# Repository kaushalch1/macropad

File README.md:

Smart OLED MacroPad

A customizable MacroPad with an OLED display, designed to provide quick access to essential travel and utility tools.

## Features
Google Maps launcher,
Weather information,
Currency converter,
Travel checklist,
OLED display interface,
One-key access to commonly used functions,
Plug-and-play operation,
The customize of buttons is released soon with the help of qmk software.
The oled display shows the time.

## software
kicad
fusion360
qmk

## Parts(or)bom
SEED XIAO board,
4 mx switches,
1 oled 0.91" screen

## Schematics

## PCB

## 3D view

## cad photo

## travel photo

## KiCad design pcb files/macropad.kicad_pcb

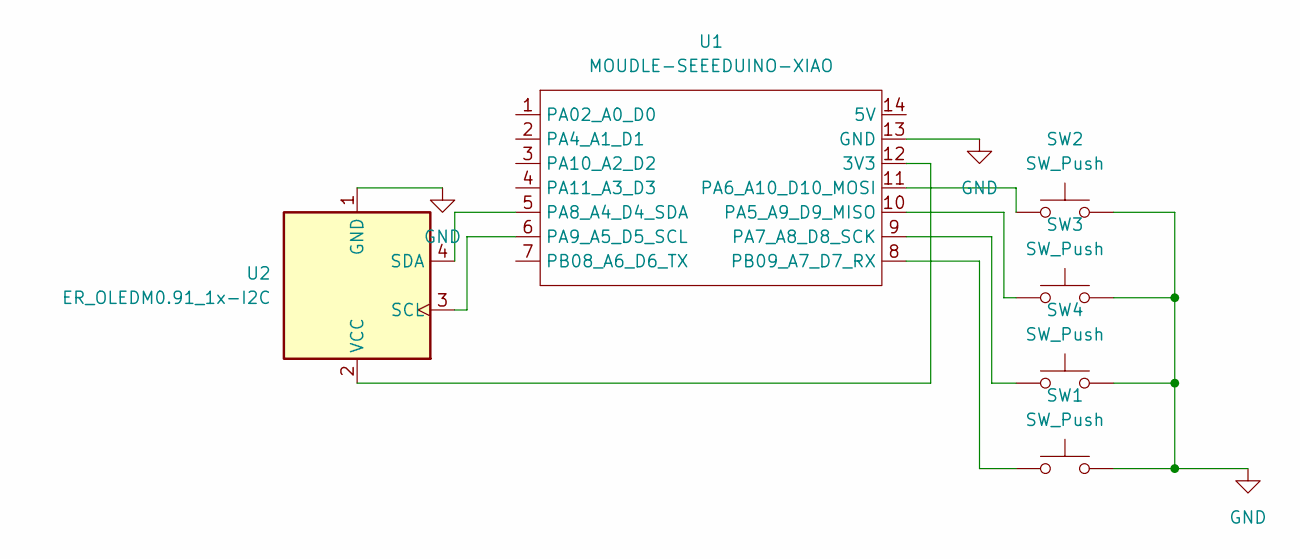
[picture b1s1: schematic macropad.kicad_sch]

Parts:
SW1, SW2, SW3, SW4: SW_Push; SW_Cherry_MX_1.00u_PCB
U1: MOUDLE-SEEEDUINO-XIAO; XIAO-Generic-Hybrid-14P-2.54-21X17.8MM
U2: ER_OLEDM0.91_1x-I2C

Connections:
GND: SW1.2, SW2.2, SW3.2, SW4.2, U1.13 (GND), U2.1 (GND)
unnamed: U1.12 (3V3), U2.2 (VCC)
unnamed: SW3.1, U1.10 (PA5_A9_D9_MISO)
unnamed: SW2.1, U1.11 (PA6_A10_D10_MOSI)
unnamed: SW4.1, U1.9 (PA7_A8_D8_SCK)
unnamed: U1.5 (PA8_A4_D4_SDA), U2.4 (SDA)
unnamed: U1.6 (PA9_A5_D5_SCL), U2.3 (SCL)
unnamed: SW1.1, U1.8 (PB09_A7_D7_RX)

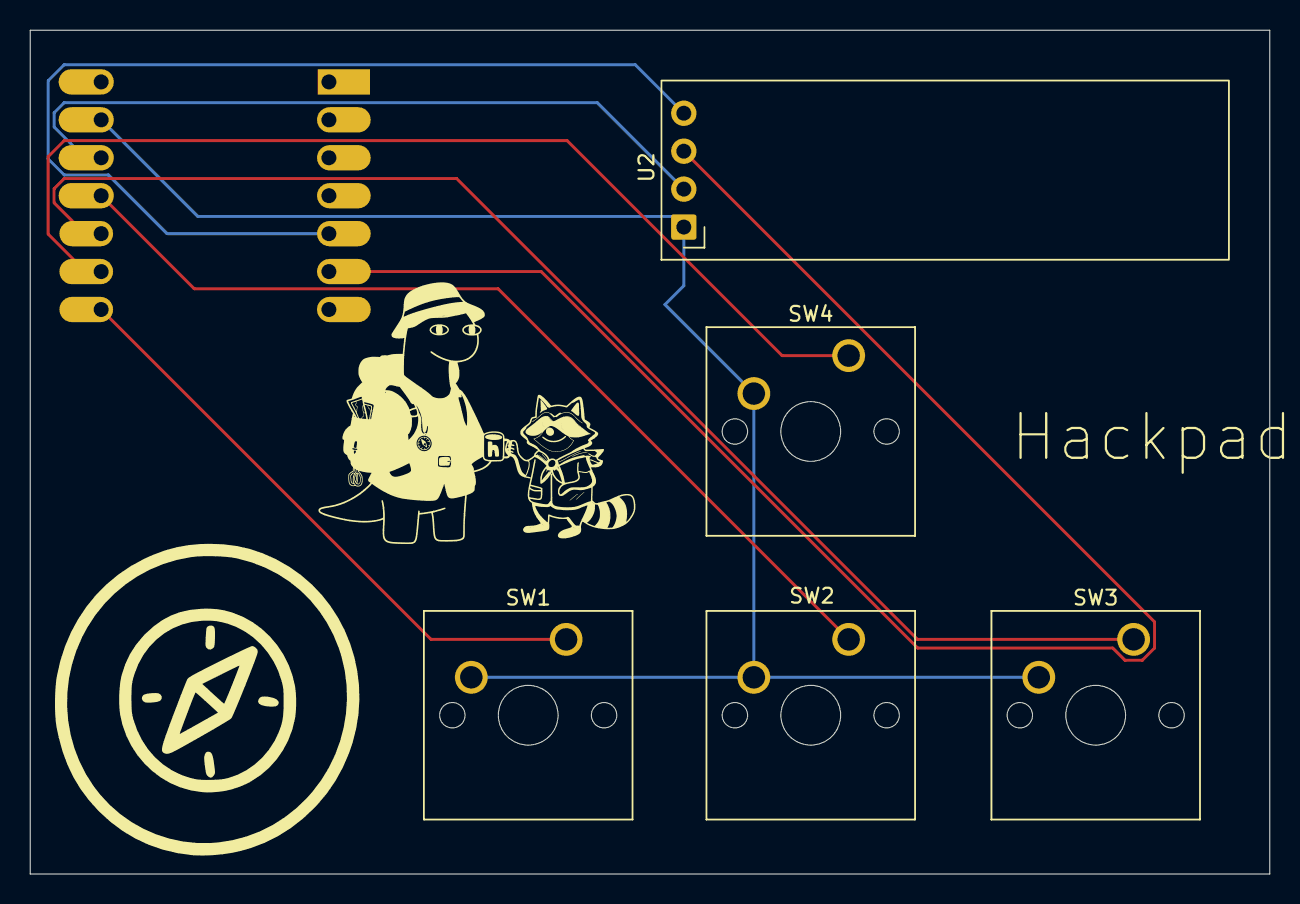
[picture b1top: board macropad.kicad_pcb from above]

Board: 2 copper layers, 83.0 x 56.5 mm, 6 parts (1 on the bottom side), 8 nets.
